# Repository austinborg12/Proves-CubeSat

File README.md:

# Proves-CubeSat
Proves CubeSat Hardware design.

Feel free to upload whatever project files you have to a new branch, just name it after yourself so its easy to see who is working on what.

ToDo:
Create doc to explain how GitHub works
Maybe get a desktop program to make the interface clearer

Build some shit

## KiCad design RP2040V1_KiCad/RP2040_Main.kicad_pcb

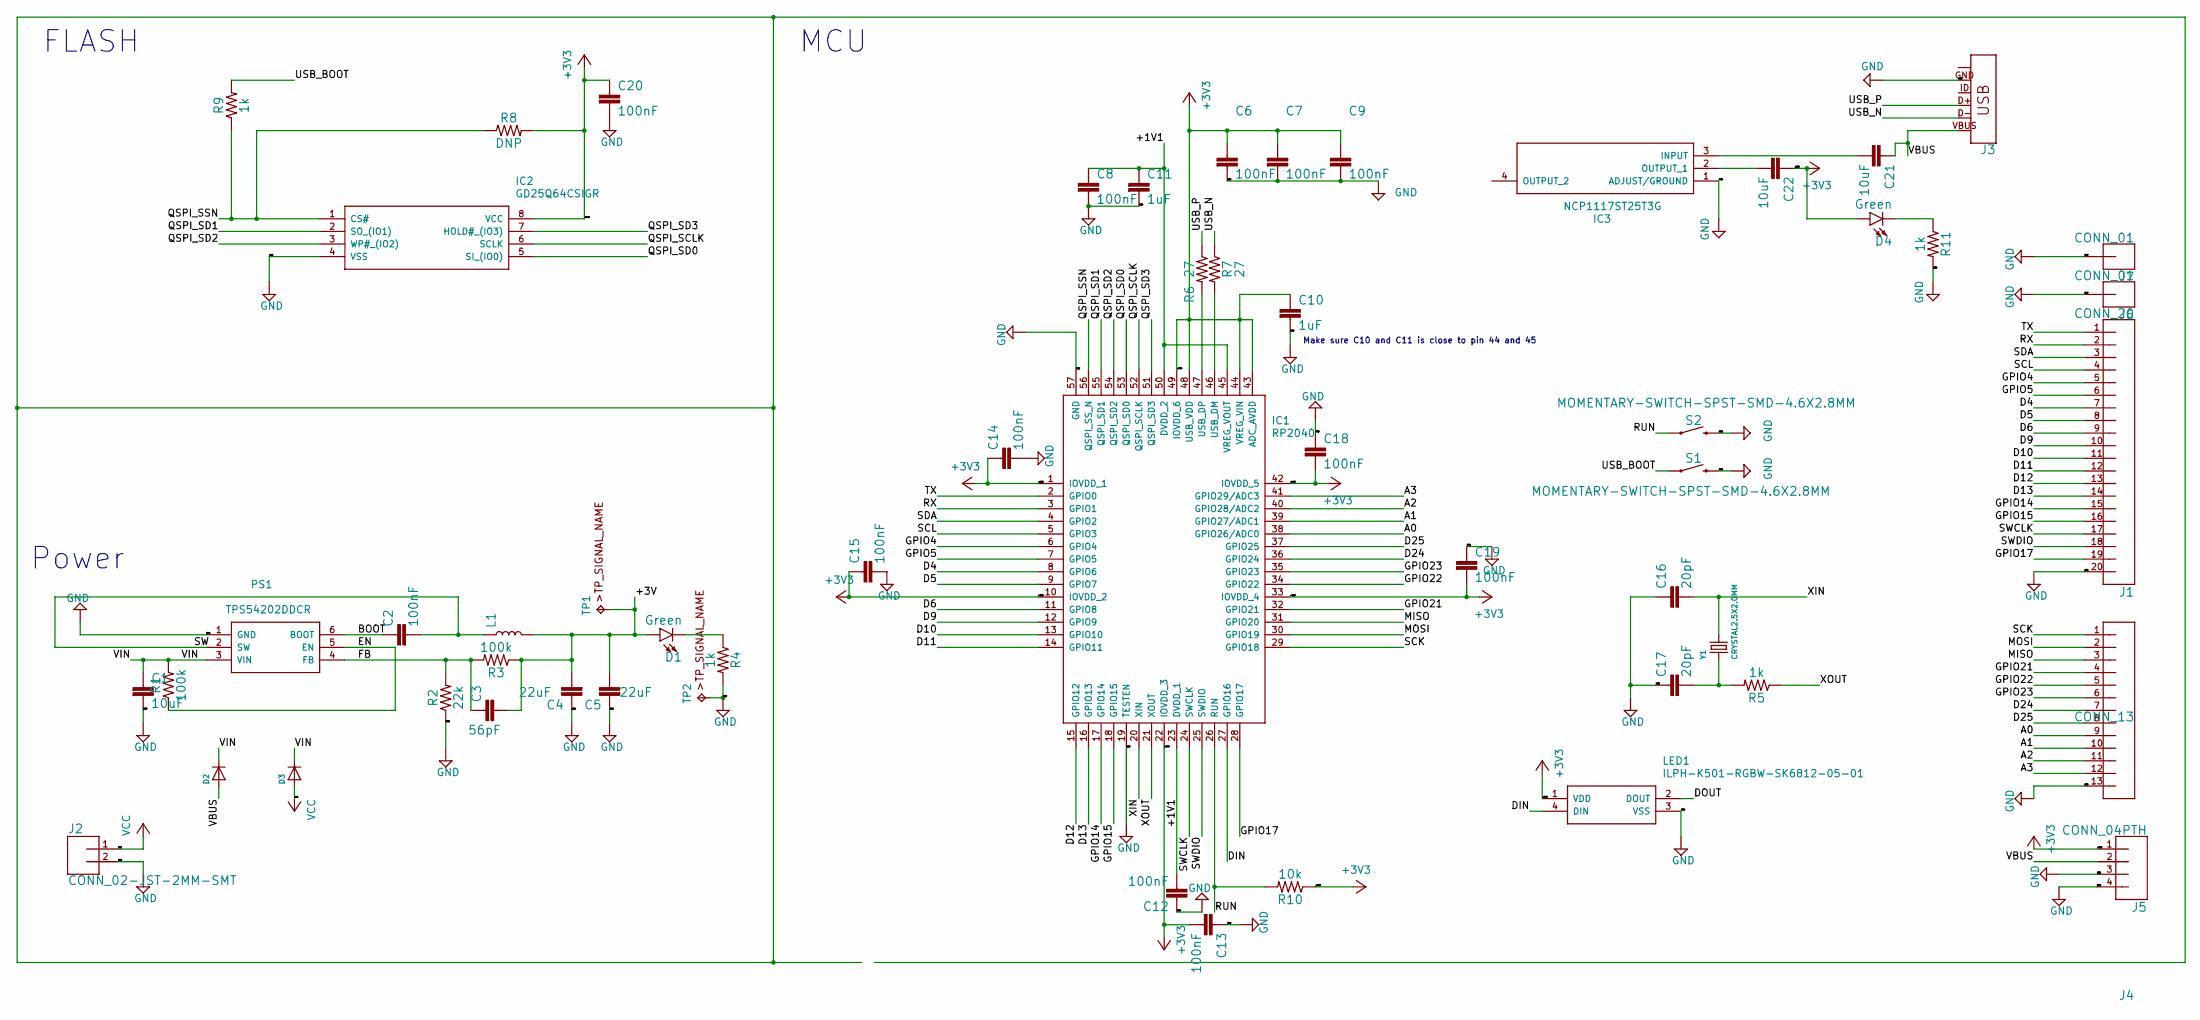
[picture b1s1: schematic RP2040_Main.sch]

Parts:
C1: 10uF; 1206
C2, C20: 100nF; 0603
C3: 56pF; 0603
C4, C5: 22uF; 1210
C6, C7, C8, C9, C12, C13, C14, C15, C18, C19: 100nF; 0402
C10, C11: 1uF; 0402
C16, C17: 20pF; 0603
C21, C22: 10uF; 0603
D1, D4: Green; LED-0603
D2, D3: 3A/10V/280mV; SOD-123
IC1: RP2040; QFN40P700X700X90-57N
IC2: GD25Q64CSIGR; SOIC127P790X216-8N
IC3: NCP1117ST25T3G; SOT230P700X180-4N
J1: CONN_20; 1X20
J2: CONN_02-JST-2MM-SMT; JST-2-SMD
J3: USB Type Micro-B Connector; USB-MICROB-PTH-MILL
J4: CONN_13; 1X13
J5: CONN_04PTH; 1X04
J6, J7: CONN_01; 1X01
L1: 68µH/±20%/1.05A; CR75
LED1: ILPH-K501-RGBW-SK6812-05-01; ILPHK501RGBWSK68120501
PS1: TPS54202DDCR; SOT95P280X110-6N
R1, R3: 100k; 0603
R2: 22k; 0603
R4, R5, R9, R11: 1k; 0603
R6, R7: 27; 0603
R8: DNP; 0603
R10: 10k; 0603
S1, S2: MOMENTARY-SWITCH-SPST-SMD-4.6X2.8MM; TACTILE_SWITCH_SMD_4.6X2.8MM
TP1, TP2: TPB1,27; B1,27
Y1: CRYSTAL2.5X2.0MM; CRYSTAL_2.5X2

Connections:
+3V3: C6.1, C7.1, C9.1, C10.1, C13.2, C14.1, C15.1, C18.2, C19.2, C20.1, C22.1, D4.A, IC1.1 (IOVDD_1), IC1.10 (IOVDD_2), IC1.22 (IOVDD_3), IC1.33 (IOVDD_4), IC1.42 (IOVDD_5), IC1.43 (ADC_AVDD), IC1.44 (VREG_VIN), IC1.48 (USB_VDD), IC1.49 (IOVDD_6), IC2.8 (VCC), J5.1, LED1.1 (VDD), R8.2, R10.1
/+1V1: C8.1, C11.1, C12.2, IC1.23 (DVDD_1), IC1.45 (VREG_VOUT), IC1.50 (DVDD_2)
/+3V: C3.2, C4.2, C5.2, D1.A, L1.P$2 (2), R3.1, TP1.TP
/A0: IC1.38 (GPIO26/ADC0), J4.9
/A1: IC1.39 (GPIO27/ADC1), J4.10
/A2: IC1.40 (GPIO28/ADC2), J4.11
/A3: IC1.41 (GPIO29/ADC3), J4.12
/BOOT: C2.1, PS1.6 (BOOT)
/D4: IC1.8 (GPIO6), J1.7
/D5: IC1.9 (GPIO7), J1.8
/D6: IC1.11 (GPIO8), J1.9
/D9: IC1.12 (GPIO9), J1.10
/D10: IC1.13 (GPIO10), J1.11
/D11: IC1.14 (GPIO11), J1.12
/D12: IC1.15 (GPIO12), J1.13
/D13: IC1.16 (GPIO13), J1.14
/D24: IC1.36 (GPIO24), J4.7
/D25: IC1.37 (GPIO25), J4.8
/DIN: IC1.27 (GPIO16), LED1.4 (DIN)
/DOUT: LED1.2 (DOUT)
/EN: PS1.5 (EN), R1.1
/FB: C3.1, PS1.4 (FB), R2.2, R3.2
/GPIO4: IC1.6 (GPIO4), J1.5
/GPIO5: IC1.7 (GPIO5), J1.6
/GPIO14: IC1.17 (GPIO14), J1.15
/GPIO15: IC1.18 (GPIO15), J1.16
/GPIO17: IC1.28 (GPIO17), J1.19
/GPIO21: IC1.32 (GPIO21), J4.4
/GPIO22: IC1.34 (GPIO22), J4.5
/GPIO23: IC1.35 (GPIO23), J4.6
/MISO: IC1.31 (GPIO20), J4.3
/MOSI: IC1.30 (GPIO19), J4.2
/QSPI_SCLK: IC1.52 (QSPI_SCLK), IC2.6 (SCLK)
/QSPI_SD0: IC1.53 (QSPI_SD0), IC2.5 (SI_(IO0))
/QSPI_SD1: IC1.55 (QSPI_SD1), IC2.2 (SO_(IO1))
/QSPI_SD2: IC1.54 (QSPI_SD2), IC2.3 (WP#_(IO2))
/QSPI_SD3: IC1.51 (QSPI_SD3), IC2.7 (HOLD#_(IO3))
/QSPI_SSN: IC1.56 (QSPI_SS_N), IC2.1 (CS#), R8.1, R9.1
/RUN: IC1.26 (RUN), R10.2, S2.1, S2.2 (1)
/RX: IC1.3 (GPIO1), J1.2
/SCK: IC1.29 (GPIO18), J4.1
/SCL: IC1.5 (GPIO3), J1.4
/SDA: IC1.4 (GPIO2), J1.3
/SW: C2.2, L1.P$1 (1), PS1.2 (SW)
/SWCLK: IC1.24 (SWCLK), J1.17
/SWDIO: IC1.25 (SWDIO), J1.18
/TX: IC1.2 (GPIO0), J1.1
/USB_BOOT: R9.2, S1.1, S1.2 (1)
/USB_N: J3.D-, R7.1
/USB_P: J3.D+, R6.1
/VBUS: C21.1, D2.A, J3.VBUS, J5.2
/VIN: C1.1, D2.C, D3.C, PS1.3 (VIN), R1.2
/XIN: C16.2, IC1.20 (XIN), Y1.3 (2)
/XOUT: IC1.21 (XOUT), R5.1
GND: C1.2, C4.1, C5.1, C6.2, C7.2, C8.2, C9.2, C10.2, C11.2, C12.1, C13.1, C14.2, C15.2, C16.1, C17.1, C18.1, C19.1, C20.2, IC1.19 (TESTEN), IC1.57 (GND), IC2.4 (VSS), IC3.1 (ADJUST/GROUND), J1.20, J2.2 (1), J3.GND, J4.13, J5.3, J5.4, J6.1, J7.1, LED1.3 (VSS), PS1.1 (GND), R2.1, R4.2, R11.2, S1.3 (2), S1.4 (2), S2.3 (2), S2.4 (2), TP2.TP
unnamed: C17.2, R5.2, Y1.1
unnamed: C21.2, IC3.3 (INPUT)
unnamed: C22.2, IC3.2 (OUTPUT_1)
unnamed: D1.C, R4.1
unnamed: D4.C, R11.1
unnamed: IC1.46 (USB_DM), R7.2
unnamed: IC1.47 (USB_DP), R6.2
unnamed: J3.SHIELD, J3.SHIELD2 (SHIELD), J3.SHIELD3 (SHIELD), J3.SHIELD4 (SHIELD), J3.SHIELD5 (SHIELD), J3.SHIELD6 (SHIELD), J3.SHIELD7 (SHIELD), J3.SHIELD8 (SHIELD), J3.SHIELD9 (SHIELD), J3.SHIELD10 (SHIELD)
VCC: D3.A, J2.1 (2)

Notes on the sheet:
Power
MCU
FLASH
Make sure C10 and C11 is close to pin 44 and 45

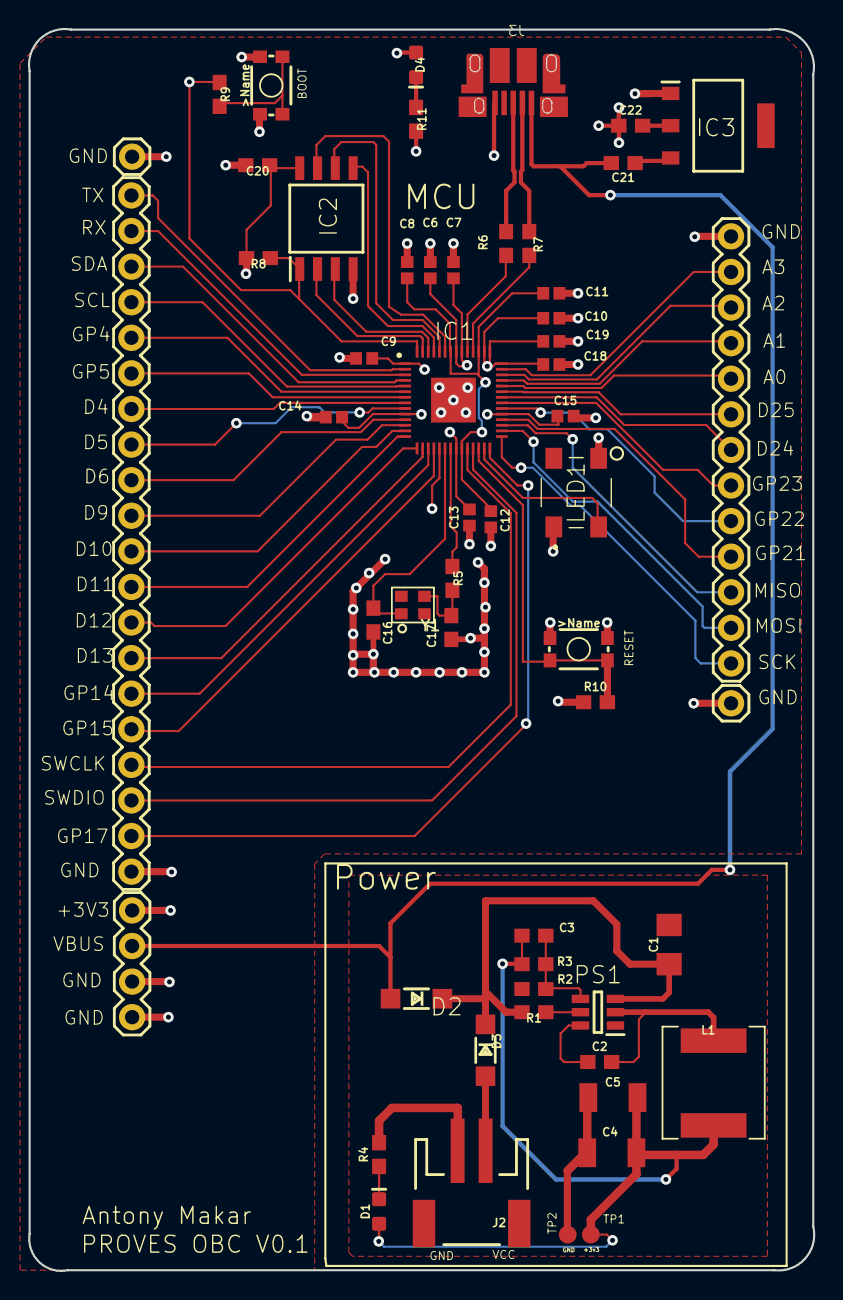
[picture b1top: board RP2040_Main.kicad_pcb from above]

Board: 4 copper layers, 56.0 x 88.6 mm, 55 parts (0 on the bottom side), 63 nets.
